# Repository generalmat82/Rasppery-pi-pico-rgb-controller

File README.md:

This Project was a project I started when I was in need of a RGB controller for rgb strips I had on my desk. I thus decided to make it a lot more expensive by doing it myself!
I wanted to be able to controll the RGB strips from my computer, I also wanted it to be mostly made by me.

I separated the project into 3 parts:
* Frontend
  * This would be the section with a webpage to controll the controller. 
* Backend
  * This would be the place where all the current values was being saved; With a bit of moddifications we could get rid of this section entirely.
* Controller
  * Finally this is the place that actually controlls the rgb strips.

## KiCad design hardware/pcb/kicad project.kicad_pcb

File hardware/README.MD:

This section of the repositary is for the hardware nececity of the project.

# Project nececity:
When I started the project I wanted to be able to controll the 2 RGB strips on my desk through WIFI since the remotes were pretty broken and why not?
The project needed the following:
* Be able to run both RGB strips separately.
* Be able to controll them with my computer.
* Be fully made by me(except the components and things I couldnt do myself)

# Hardware components:
For the project I used:
* 3 [IRLB8721PBF-ND](https://www.digikey.ca/en/products/detail/infineon-technologies/IRLB8721PBF/2127670) per strips
* 1 [RASPBERRY PI PICO W RP2040](https://www.digikey.ca/en/products/detail/raspberry-pi/SC0918/16608263)
* 1 [S7002-ND](https://www.digikey.ca/en/products/detail/sullins-connector-solutions/PPTC041LFBN-RC/810144) per strips
* I also had a laptop running Ubuntu for the front end and backend that was communicating with the RPI Pico W.

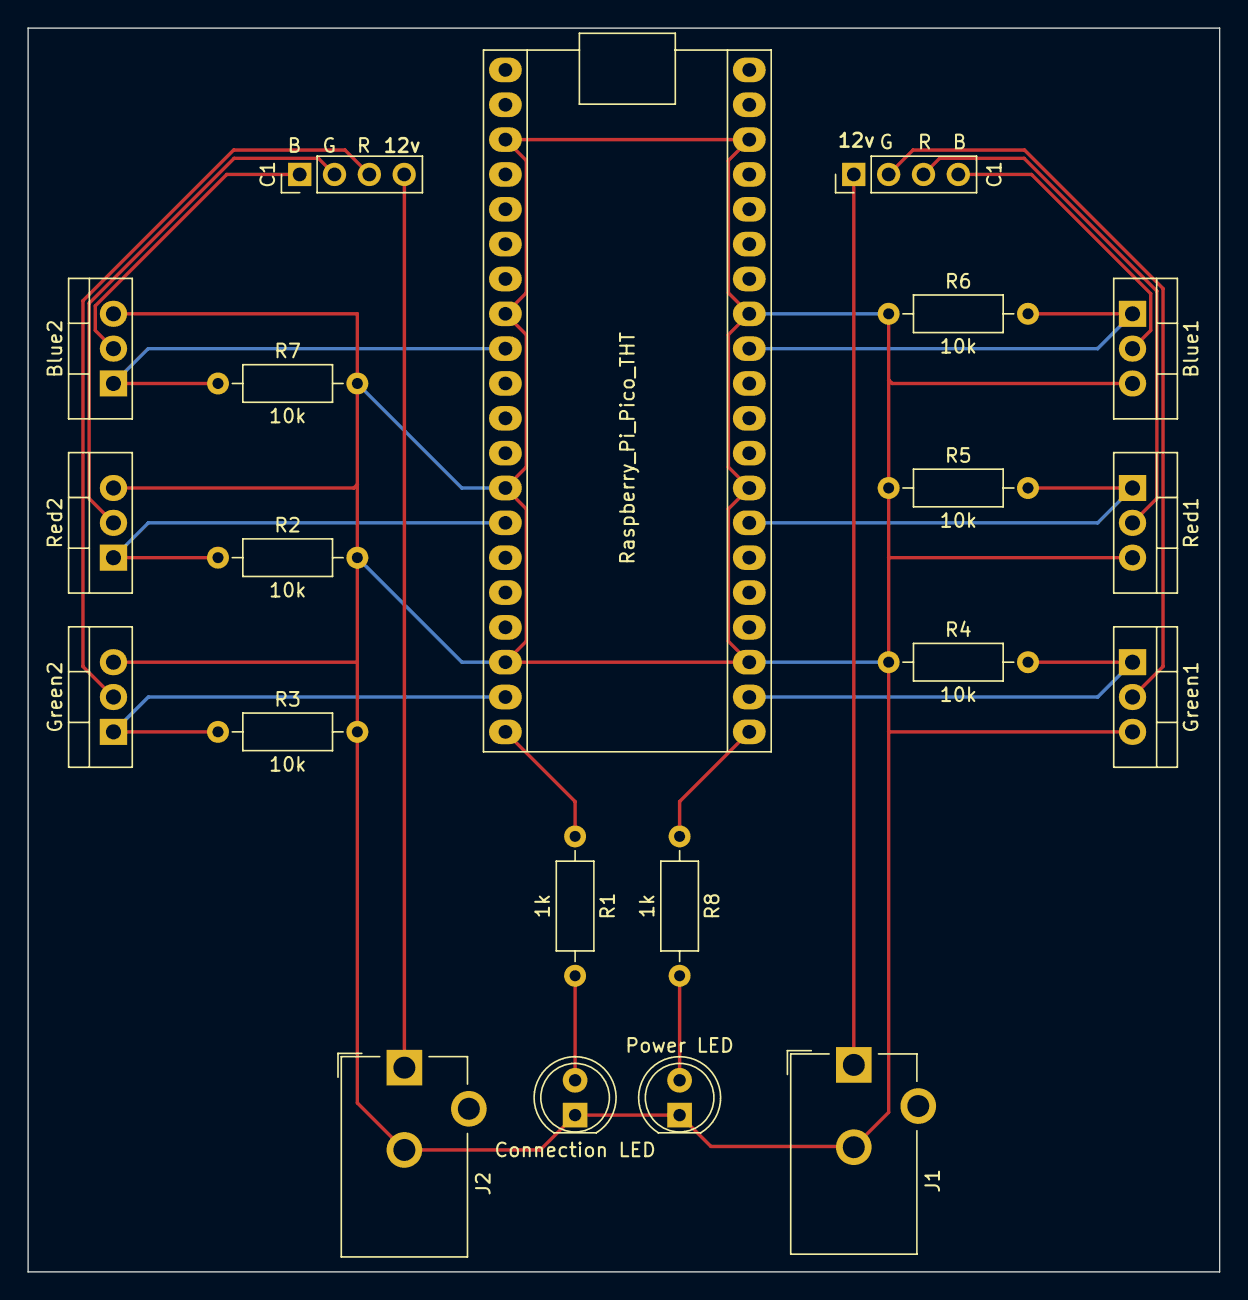
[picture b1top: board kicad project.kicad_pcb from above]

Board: 2 copper layers, 86.9 x 90.7 mm, 21 parts (0 on the bottom side), 19 nets.

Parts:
A1: Raspberry_Pi_Pico_THT; raspberry_pi_pico_THT
Blue1, Blue2: IRLB8721PBF; TO-220-3_Vertical
C1, C1#2: Conn_01x04_Socket; PinHeader_1x04_P2.54mm_Vertical
Connection LED: LED; LED_D5.0mm
Green1, Green2: IRLB8721PBF; TO-220-3_Vertical
J1, J2: Barrel_Jack_Switch; BarrelJack_CUI_PJ-102AH_Horizontal
Power LED: LED; LED_D5.0mm
R1, R8: 1k; R_Axial_DIN0207_L6.3mm_D2.5mm_P10.16mm_Horizontal
R2, R3, R4, R5, R6, R7: 10k; R_Axial_DIN0207_L6.3mm_D2.5mm_P10.16mm_Horizontal
Red1, Red2: IRLB8721PBF; TO-220-3_Vertical

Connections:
unnamed: A1.32 (ADC1/GP27), Blue1.1 (G), R6.2
unnamed: A1.9 (GP6), Blue2.1 (G), R7.1
unnamed: A1.14 (GP10), R2.1, Red2.1 (G)
unnamed: A1.19 (GP14), Green2.1 (G), R3.1
unnamed: A1.20 (GP15), R1.1
unnamed: A1.21 (GP16), R8.1
unnamed: A1.22 (GP17), Green1.1 (G), R4.2
unnamed: A1.27 (GP21), R5.2, Red1.1 (G)
unnamed: Blue1.2 (D), C1.4
unnamed: A1.3 (GND), A1.8 (GND), A1.13 (GND), A1.18 (GND), A1.23 (GND), A1.28 (GND), A1.33 (GND), A1.38 (GND), Blue1.3 (S), Blue2.3 (S), Connection LED.1, Green1.3 (S), Green2.3 (S), J1.2, J2.2, Power LED.1, R2.2, R3.2, R4.1, R5.1, R6.1, R7.2, Red1.3 (S), Red2.3 (S)
unnamed: Blue2.2 (D), C1#2.1
unnamed: Connection LED.2, R1.2
unnamed: C1.2, Green1.2 (D)
unnamed: C1#2.3, Green2.2 (D)
unnamed: C1#2.2, Red2.2 (D)
unnamed: C1#2.4, J2.1
unnamed: C1.1, J1.1
unnamed: C1.3, Red1.2 (D)
unnamed: Power LED.2, R8.2

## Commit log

2023-08-21 creeating repo
2023-08-22 made good looking buttons
2023-08-22 did stuff
2023-08-23 made some style changes made the value of ranges editable
2023-08-28 tryed to fix it up had issues
2023-12-07 trying to sync in
2023-12-07 for adding info about hardware
2023-12-08 Moving stuff out
